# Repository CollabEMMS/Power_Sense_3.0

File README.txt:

README.txt
Power Sense v3.1.2
@author: Joe Wambach
@LastEditor: Joe Wambach		<----------------------- UPDATE THIS WHOEVER LAST EDITS THIS

last edit to this document: 2/21/19

Revision History:

	3.0:	Initial version of new power sense
	3.1: 	Removed Murata Transformer
		Removed R1
		Added Test Headers for CH0+, CH1+, HFout, Fout0, Fout1
		Added Triad Transformer
		Added Resistor Divider to bypass transformer circuitry
	3.1.1:	Changed connection for test header from CH1+ to CH1-
		R5 --> 20k 1%
	3.1.2:	Removed R15 and R16
		Fixed Connection to +5V on SPI Connector

Edits to be made in the future:
	- Fix issue with test header for CH1. Either flip connections to filters so CH1- is connected to GND. OR just change the connection for the test header from CH1+ to CH1-.
		DONE

	⁃ Fix circuitry so that resistor divider (bypassing transformer) and resistor divider (on transformer secondary) don’t connect and interfere with each other. OR just develop a good method to assemble boards with only one set of resistors or the other.

	⁃ Change resistor values on transformer secondary. It currently uses 10k and 1k to scale down by 11. This works for 120Vrms since transformer will output about 6Vp so MCP will get ~600mV. However, if 240Vrms connect to primary coils, 12Vp comes out of secondary meaning MCP will see 1.2Vp which is > 660mV maximum rating.
		DONE

	- Fix silkscreen part numbers and values

	- Fix trace connection to +5V of SPI because it barely touches it 
		DONE
	
	- Get rid of R16 and R15 because they prevent communication from working
		DONE

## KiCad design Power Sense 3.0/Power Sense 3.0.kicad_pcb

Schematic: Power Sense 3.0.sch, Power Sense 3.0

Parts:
C1, C2, C3, C4, C5, C6, C10: 100nF; C_Disc_D3.0mm_W1.6mm_P2.50mm
C7: 4.7uF; C_Disc_D3.0mm_W1.6mm_P2.50mm
C8, C9: 27pF; C_Disc_D3.0mm_W1.6mm_P2.50mm
D1, D2, D3: LED; LED_D5.0mm
IC1: MCP3909; mcp3909-i&slash_ss
J1: Power; Pin_Header_Straight_1x02_Pitch2.54mm
J2: ProgHead; Pin_Header_Straight_1x05_Pitch2.54mm
J3: SPI; PinHeader_1x07_P2.54mm_Vertical
J4: TestHeader; PinHeader_1x06_P2.54mm_Vertical
R1: 536k; R_Axial_DIN0204_L3.6mm_D1.6mm_P7.62mm_Horizontal
R2, R3: 10 1%; R_Axial_DIN0204_L3.6mm_D1.6mm_P7.62mm_Horizontal
R4, R6, R7, R8, R9, R12, R17, R18, R19, R21: 1k; R_Axial_DIN0204_L3.6mm_D1.6mm_P7.62mm_Horizontal
R5: 20k 1%; R_Axial_DIN0204_L3.6mm_D1.6mm_P7.62mm_Horizontal
R10, R22, R23: 330; R_Axial_DIN0204_L3.6mm_D1.6mm_P7.62mm_Horizontal
R11, R14: 10; R_Axial_DIN0204_L3.6mm_D1.6mm_P7.62mm_Horizontal
R13: 10k; R_Axial_DIN0204_L3.6mm_D1.6mm_P7.62mm_Horizontal
R20, R24: 0; R_Axial_DIN0204_L3.6mm_D1.6mm_P7.62mm_Horizontal
T1: AC1030
T2: 2p2sTransformer; Transformer FS12-090-C2
U1: PIC18F25K20_I/SS; PIC18F25K22-I_SP
Y1: 3.579545MHz Crystal; CXO_3_579545_MHz

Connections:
/5V_PULL_UP: J2.1, R13.2, U1.1 (~MCLR~/RE3)
/+5V: C7.2, J2.2, J3.5, R11.2, R13.1, R14.2
/+12V: J3.7
/CH0+: C1.2, IC1.5 (CH0+), J4.5, R6.2
/CH1+: C4.1, IC1.8 (CH1+), R9.2
/CH1-: C3.2, IC1.7 (CH1-), J4.4, R8.2
/CHIP_SELECT: J3.4, U1.21 (AN12/INT0/RB0)
/Fo0toPIC: IC1.24 (FOUT0), J4.1, U1.4 (RA2/Vref-AN2)
/Fo1toPIC: IC1.23 (FOUT1), J4.2, U1.6 (RA4)
/H: J1.1, R20.2, T2.1
/HFtoPIC: IC1.22 (HFOUT), J4.3, U1.5 (RA3/Vref+AN3)
/LED_TO_11: R22.2, U1.11 (RC0)
/LED_TO_12: R23.2, U1.12 (CCP2/RC1)
/LED_TO_25: R10.2, U1.25 (AN11/RB4)
/MCLR: IC1.9 (MCLR'), U1.17 (TX/RC6)
/MCP_CS_TO_PIC: IC1.14 (F0/CS'), R21.1
/N: J1.2, R24.2, T2.4
/PROG_CLK: J2.4, U1.28 (PGD/RB7)
/PROG_DI: J2.5, U1.27 (PGC/RB6)
/SCK: IC1.12 (F2/SCK), R17.1
/SDI: IC1.13 (F1/SDI), R18.1
/SDO: IC1.20 (NEG/SDO), R19.1
/SPI_CLK: J3.3, U1.22 (AN10/INT1/RB1)
/SPI_MD_IN: J3.1, U1.24 (AN9/RB3)
/SPI_MD_OUT: J3.2, U1.23 (AN8/INT2/RB2)
GND: C1.1, C2.2, C3.1, C4.2, C5.2, C6.1, C7.1, C8.2, C9.2, C10.2, D1.1, D2.1, D3.1, IC1.11 (AGND), IC1.15 (G1), IC1.16 (G0), IC1.21 (DGND), J2.3, J3.6, J4.6, R2.2, R3.1, R4.1, R9.1, R12.1, R24.1, T2.6, U1.8 (Vss), U1.19 (Vss)
unnamed: C2.1, IC1.6 (CH0-), R7.2
unnamed: C5.1, IC1.10 (REF_IN/OUT)
unnamed: C6.2, IC1.1 (DVDD), IC1.2 (HPF), IC1.3 (AVDD), R11.1
unnamed: C8.1, IC1.18 (CLKOUT), Y1.1
unnamed: C9.1, IC1.17 (CLKIN), Y1.2
unnamed: C10.1, R14.1, U1.20 (Vdd)
unnamed: D1.2, R10.1
unnamed: D2.2, R22.1
unnamed: D3.2, R23.1
unnamed: R1.1, R4.2, R5.1, R8.1, R12.2
unnamed: R1.2, R20.1
unnamed: R2.1, R6.1, T1.1
unnamed: R3.2, R7.1, T1.2
unnamed: R5.2, T2.5
unnamed: R17.2, U1.14 (SCL/SCK/RC3)
unnamed: R18.2, U1.15 (SDA/SDI/RC4)
unnamed: R19.2, U1.16 (SDO/RC5)
unnamed: R21.2, U1.18 (RX/RC7)
unnamed: T2.2, T2.3

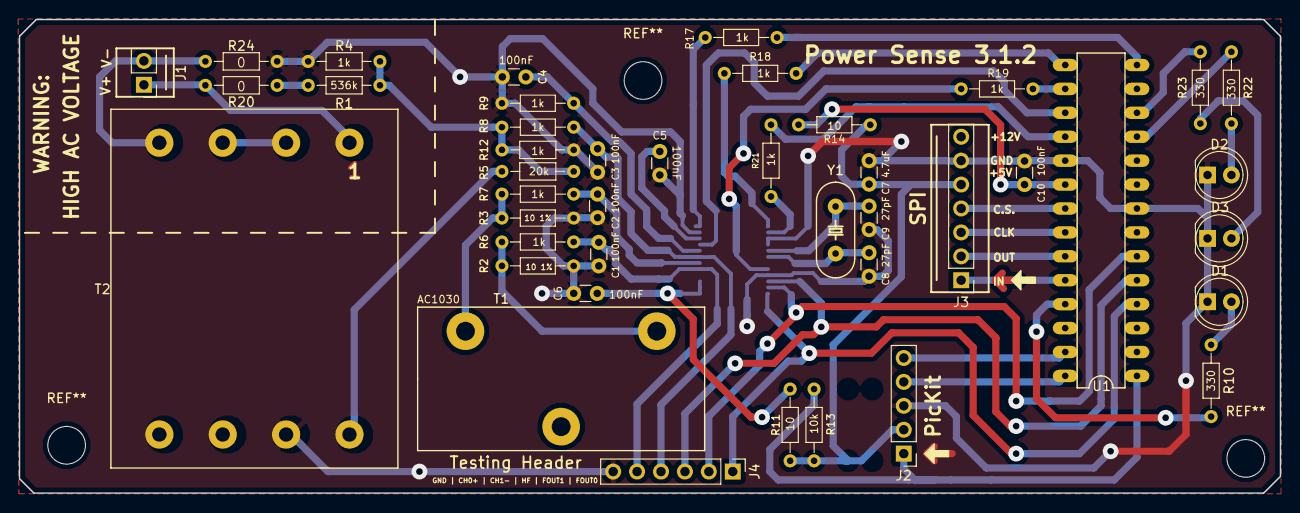
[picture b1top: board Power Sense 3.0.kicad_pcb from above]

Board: 2 copper layers, 133.9 x 50.3 mm, 44 parts (1 on the bottom side), 44 nets.

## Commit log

2018-03-29 Inital Commit
    Add pcb, schematic, and libraries to repository
2018-04-17 Updated files with new files
2018-04-19 Load Cap Change
    Change load capacitors from 30 pF to 27 pF
2018-04-24 PCB Layout Changes
    Increased the width and height of the board slightly. Components were moved, and traces were redone.
2018-11-27 Initial commit
    - Created new branch for 3.1.
    - Remapped symbols to schematic.
    - Deleted CH1 circuitry
    - Removed resistor from MCLR since it was removed during breadboard prototyping
2018-11-29 Added transformer for CH1
    Put new transformer sch symbol
2018-11-29 Create Transformer FS12-090-C2.kicad_mod
    Added Layout Pattern for FS12-090-C2 transformer
2018-11-29 Added new CH1 circuitry
    Added transformer circuitry and resistor divider for CH1 of MCP
2018-11-29 Updated schematic for Power Sense
    Updated schematic for Power Sense to include new transformer and resistor divider components.
    **Incomplete PCB Layout**
2018-11-30 Finished Version of initial v3.1
    Added connections to all new parts and added silkscreen components
2018-12-01 Added Pin 1 reference for transformer
    Added "1" by pin 1 on transformer in both silkscreen and coppe
2018-12-01 Milling Files for initial PCB prototype
    Generated gerber files for milling for the initial PCB prototypes
2018-12-07 Added README.txt
    README.txt includes notes such as future edits
2019-02-07 First round of edits
    Edited things in README.txt
    See that file for changes
2019-02-14 Changed Transformer Resistor Divider R value
    Changed 10k to 20k for 240v use
2019-02-21 3.1.1
    Edited Test Header Connection
    Changed resistor value
    See README.txt for more info
2019-02-21 3.1.2
    Removed two resistors in SCH and PCB
    Fixed 5V connection on SPI connector
2019-02-21 3.1.2
    Updated Silkscreen Labels
2019-02-28 Silkscreen fix
    Add silkscreen to the power sense board.
2019-03-07 PCB Fix
2019-03-15 Gerbers

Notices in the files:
parts and their libraries:
Copyright 2016 Accelerated Designs. All rights reserved.
